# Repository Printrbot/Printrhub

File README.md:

# Printrhub

Welcome and thank you for your interest in our Printrhub technology. In this repository you will find everything you need to build upon the technology we invented. You may use the code and hardware to build your own devices or to improve your own Simple 2016. Please let us know about your projects and post issues or pull request to help us improve this project and code base.

## Purpose of the Printrhub

The Printrhub is the display component of our 3D printer Simple 2016 (http://printrbot.com/new-2016-simple/) and thus is the main user interface. The user can select, start, modify and pause prints or setup the printer with it. A fluid user interface controlled by touch as you know it from your smartphone let's anyone can start a print. The Hub also controls the printer and handles communication with the Printrbot cloud.

The Printrhub contains these components that form the final hardware

* ESP-12E module for WiFi connection and Over the Air updates
* MK20DX256LHV7 (Teensy 3) MCU is the main processor for handling the display, touch, SD card, controls the printer and ESP-12E
* 2.8 inch TFT display with 320x240 pixels
* Capacitive touch screen
* microSD card slot

As our board hosts two MCUs we need two different firmware, one for the ESP-12E module and the other one for the main MCU.

## Organization of this repository

* **/esp**: The firmware for the ESP-12E WiFi module
* **/mk20**: Contains the firmware for the main processor
* **/pcb**: Revisions 0.1, and 0.4 (final revision) of the PCB as Eagle and Copper files (for BOM and 3D views)
* **/utils**: The image tool that we use to build the ui.min file that contains all images used by the firmware combined in one file
* **/sdcard**: The initial content of the SD card that we ship with your printer (contains firmware images and root folder structure)
 
## Documentation
  
We have developed the hub in cooperation with Phillip Schuster (http://www.appfruits.com). He has written some documentation and behind the scenes reports that you should have read before working with our code and hardware.

### Behind the scenes of the Printrbot Simple 2016

How we started development and why we think you will learn something about product development in general.
http://www.appfruits.com/2016/11/behind-the-scenes-printrbot-simple-2016/

### Display System Explained

Expains the display and application framework in great detail. Explains the application flow, how to pseudo code multi threading and how implement a fast fluid and responsive user interface in a device capable of only 64 KB of RAM and 72 MHz.
http://www.appfruits.com/2016/11/printrbot-simple-2016-display-system-explained/

### CommStack explained

We invented CommStack to handle the communication between the MK20 and the ESP-12E module. It's fast, robust, bidirectional and features a nice request/response based system that enables two or more MCUs to communicate without having to handle all the little details.
http://www.appfruits.com/2016/11/printrbot-simple-2016-commstack-explained/

### Hardware explained

Describes the hardware in detail. Provides schematics, layout and details about the hardware we developed for the Printrbot hub.
http://www.appfruits.com/2016/11/printrbot-simple-2016-hardware-pcb-explained/

## Credits

Contains code or portions from these great libraries

* https://github.com/bakercp/PacketSerial
* https://github.com/PaulStoffregen/ILI9341_t3
* https://github.com/PaulStoffregen/ILI9341_fonts
* https://github.com/scanlime/esp8266-arm-swd
* https://github.com/esp8266/Arduino
* https://github.com/me-no-dev/ESPAsyncTCP.git
* https://github.com/me-no-dev/ESPAsyncWebServer.git
* https://github.com/bblanchon/ArduinoJson.git

Developed in cooperation with Phillip Schuster (@appfruits) from Appfruits (http://www.appfruits.com). Big thanks to Paul J. Stoffregen (https://www.pjrc.com/teensy/index.html) and his amazing Teensy project. It served as a great starting point and his amazing display driver for ILI9341 based display made our modern, fluid user interface possible.

## Support us

Printrbot invests time and resources providing this open source code, please support Printrbot and open-source hardware by purchasing products from Printrbot (http://www.printrbot.com)!

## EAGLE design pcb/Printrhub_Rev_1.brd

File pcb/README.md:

# Printrhub PCB

This repository contains two revisions of the PCB of the Printrhub. See main folder for more details about the project.

## Documentation and details

This PCB has been developed in cooperation by Phillip Schuster (http://www.appfruits.com). He has written a blog post about these PCBs and documents the details of it.
http://www.appfruits.com/2016/11/printrbot-simple-2016-hardware-pcb-explained/

## Revisions

This folder contains two revisions:

### Revision 0.1

This has been the first PCB we have created and contains the Teensy bootloader chip and an USB port that makes it easy to flash new firmware. It's basically just a bigger Teensy with more components. The firmware supports this revision, but you will need to set the correct #define in the HAL.h file in both firmwares

### Revision 0.4

This is the final revision we ship with the Simple 2016. Firmware must be flashed via SWD or our Over the Air update system.

## EAGLE and Copper files

These files can be opened with EAGLE, but you will need at least a Hobbyist license as we use 4-layers. We have also added Copper (http://www.copper-app.com) files that contain the complete BOM and a 3D view of the boards.

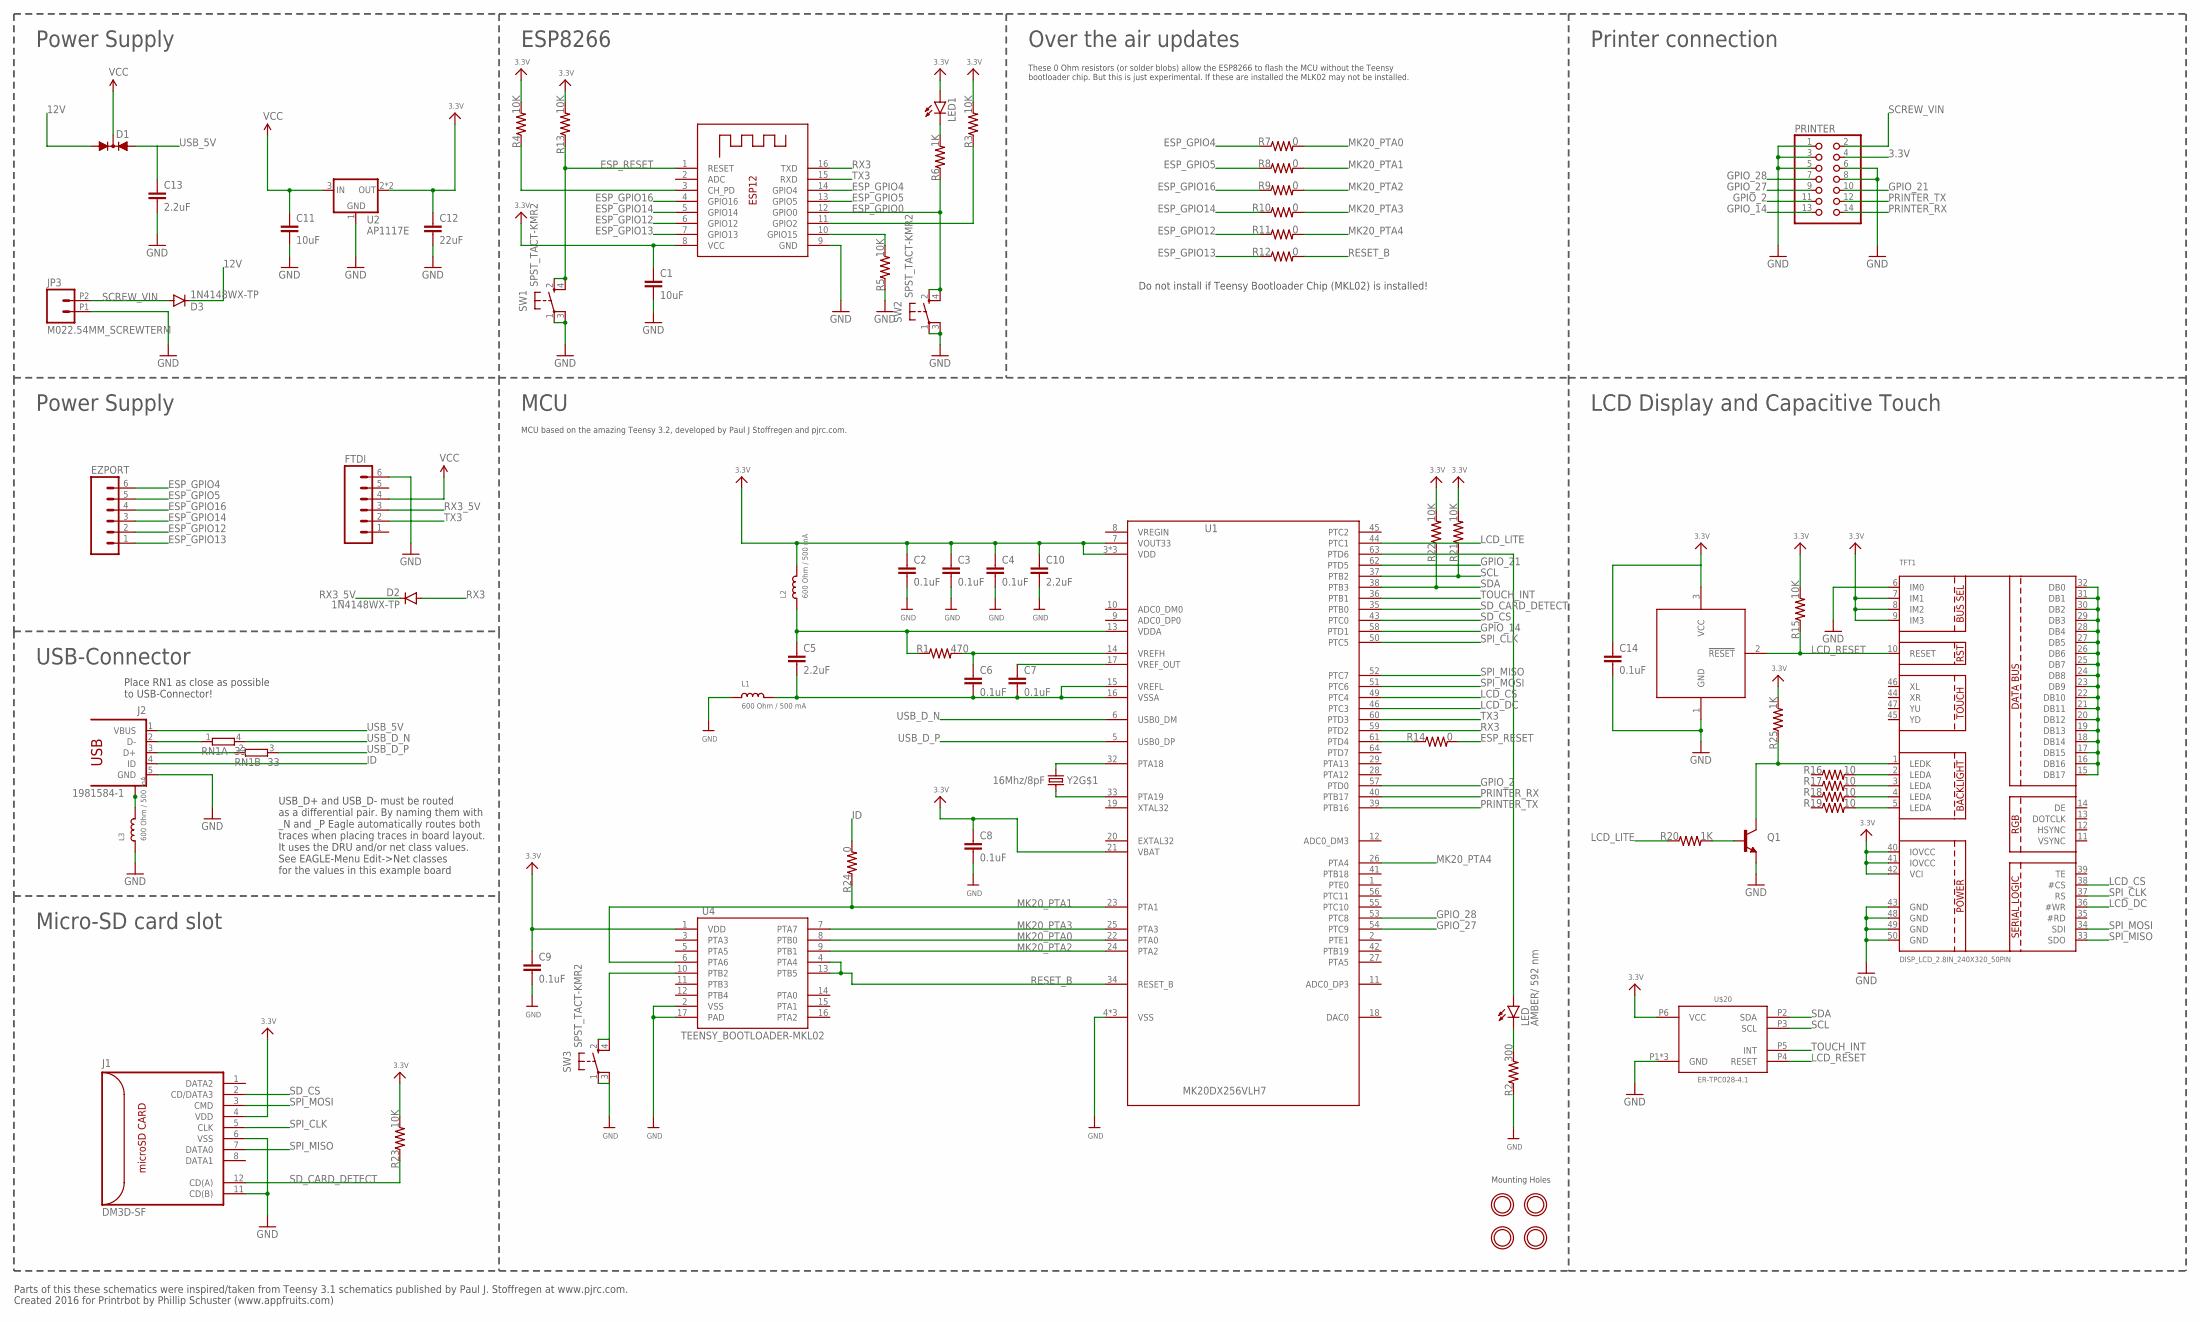
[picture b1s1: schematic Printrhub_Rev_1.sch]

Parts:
C1, C11: 10uF; 0603-CAP
C2, C3, C4, C6, C7, C8, C9, C14: 0.1uF; 0603-CAP
C5, C10, C13: 2.2uF; 0603-CAP
C12: 22uF; 0603-CAP
D1: DIODE-2AC|CASOT23; SOT23
D2, D3: 1N4148WX-TP; SOD-323; MPN 1N4148WX-TP
EZPORT: M06SMD-STRAIGHT; 1X06_SMD_STRAIGHT
FTDI: M06SMD-STRAIGHT; 1X06_SMD_STRAIGHT
J1: DM3D-SF
J2: 1981584-1
JP3: M022.54MM_SCREWTERM; 1X02_2.54_SCREWTERM
L1, L2, L3: 600 Ohm / 500 mA; 0603
LED: AMBER/ 592 nm; LED-0603
LED1: LED-GREEN; LED-0603
PRINTER: PINHD-2X7SMT; 2X07_SMT
Q1: TRANSISTOR_NPNSOT23-3; SOT23-3
R1: 470; 0603-RES
R2: 300; 0603-RES
R3, R4, R5, R13, R15, R21, R22, R23: 10K; 0603-RES
R6, R20, R25: 1K; 0603-RES
R7, R8, R9, R10, R11, R12, R14, R24: 0; 0603-RES
R16, R17, R18, R19: 10; 0603-RES
RN1: 33; EXB34V; MPN EXB-34V330JV
SW1, SW2, SW3: SPST_TACT-KMR2; KMR2
TFT1: DISP_LCD_2.8IN_240X320_50PIN; TFT_2.83IN_240X320_50PIN
U1: MK20DX256VLH7; MPN MK20DX256VLH7
U2: AP1117E; SOT223
U3: MAX308-SOT23; SOT23
U4: TEENSY_BOOTLOADER-MKL02; QFN50P300X300X100-17N
U$15, U$16, U$17, U$18: MOUNTINGHOLE2.0; MOUNTINGHOLE_2.0_PLATED
U$20: ER-TPC028-4.1; ER-CON06HB-1
X1: ESP-12
Y2: 16Mhz/8pF; CRYSTAL-SMD-5X3; MPN ECS-160-8-30B-CKM

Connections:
3.3V: C1.1, C2.1, C3.1, C4.1, C8.1, C9.1, C10.1, C12.1, C14.1, J1.4 (VDD), L2.2, LED1.A, PRINTER.4, R3.2, R4.2, R13.2, R15.2, R21.2, R22.2, R23.2, R25.2, TFT1.7 (IM1), TFT1.8 (IM2), TFT1.9 (IM3), TFT1.40 (IOVCC), TFT1.41 (IOVCC), TFT1.42 (VCI), U1.3 (VDD), U1.7 (VOUT33), U1.21 (VBAT), U1.30 (VDD), U1.48 (VDD), U2.2 (OUT), U2.4 (OUT), U3.3 (VCC), U4.1 (VDD), U$20.P6 (VCC), X1.8 (VCC)
12V: D1.1 (A1), D3.C
ESP_GPIO0: R6.1, SW2.2 (S), SW2.4 (S1), X1.12 (GPIO0)
ESP_GPIO4: EZPORT.6, R7.1, X1.14 (GPIO4)
ESP_GPIO5: EZPORT.5, R8.1, X1.13 (GPIO5)
ESP_GPIO12: EZPORT.2, R11.1, X1.6 (GPIO12)
ESP_GPIO13: EZPORT.1, R12.1, X1.7 (GPIO13)
ESP_GPIO14: EZPORT.3, R10.1, X1.5 (GPIO14)
ESP_GPIO16: EZPORT.4, R9.1, X1.4 (GPIO16)
ESP_RESET: R13.1, R14.2, SW1.2 (S), SW1.4 (S1), X1.1 (RESET)
GND: C1.2, C2.2, C3.2, C4.2, C8.2, C9.2, C10.2, C11.2, C12.2, C13.2, C14.2, FTDI.6, J1.6 (VSS), J1.11 (CD(B)), J2.5 (GND), JP3.P1 (1), L1.1, L3.1, PRINTER.1, PRINTER.3, PRINTER.5, PRINTER.6, PRINTER.8, Q1.2 (E), R2.1, R5.1, SW1.1, SW1.3 (P1), SW2.1, SW2.3 (P1), SW3.1, SW3.3 (P1), TFT1.6 (IM0), TFT1.43 (GND), TFT1.48 (GND), TFT1.49 (GND), TFT1.50 (GND), U1.4 (VSS), U1.31 (VSS), U1.47 (VSS), U2.1 (GND), U3.1 (GND), U4.2 (VSS), U4.17 (PAD), U$20.P1 (GND), U$20.PAD@0 (GND), U$20.PAD@1 (GND), X1.9 (GND)
GPIO_2: PRINTER.11, U1.57 (PTD0)
GPIO_14: PRINTER.13, U1.58 (PTD1)
GPIO_21: PRINTER.10, U1.62 (PTD5)
GPIO_27: PRINTER.9, U1.54 (PTC9)
GPIO_28: PRINTER.7, U1.53 (PTC8)
ID: J2.4 (ID), R24.2
LCD_CS: TFT1.38 (#CS), U1.49 (PTC4)
LCD_DC: TFT1.36 (#WR), U1.46 (PTC3)
LCD_LITE: R20.1, U1.44 (PTC1)
LCD_RESET: R15.1, TFT1.10 (RESET), U3.2 (!RESET), U$20.P4 (RESET)
MK20_PTA0: R7.2, U1.22 (PTA0), U4.8 (PTB0)
MK20_PTA1: R8.2, R24.1, U1.23 (PTA1), U4.6 (PTA6)
MK20_PTA2: R9.2, U1.24 (PTA2), U4.9 (PTB1)
MK20_PTA3: R10.2, U1.25 (PTA3), U4.7 (PTA7)
MK20_PTA4: R11.2, U1.26 (PTA4)
unnamed: R3.1, X1.11 (GPIO2)
unnamed: R4.1, X1.3 (CH_PD)
unnamed: R5.2, X1.10 (GPIO15)
unnamed: LED1.C, R6.2
unnamed: R14.1, U1.61 (PTD4)
unnamed: Q1.3 (C), R25.1, TFT1.1 (LEDK)
unnamed: R16.2, TFT1.2 (LEDA)
unnamed: LED.A, U1.63 (PTD6)
unnamed: R17.2, TFT1.3 (LEDA)
unnamed: R18.2, TFT1.4 (LEDA)
unnamed: R19.2, TFT1.5 (LEDA)
unnamed: Q1.1 (B), R20.2
unnamed: TFT1.15 (DB17), TFT1.16 (DB16), TFT1.17 (DB15), TFT1.18 (DB14), TFT1.19 (DB13), TFT1.20 (DB12), TFT1.21 (DB11), TFT1.22 (DB10), TFT1.23 (DB9), TFT1.24 (DB8), TFT1.25 (DB7), TFT1.26 (DB6), TFT1.27 (DB5), TFT1.28 (DB4), TFT1.29 (DB3), TFT1.30 (DB2), TFT1.31 (DB1), TFT1.32 (DB0)
unnamed: LED.C, R2.2
unnamed: U1.32 (PTA18), Y2.3 (2)
unnamed: U1.33 (PTA19), Y2.1
PRINTER_RX: PRINTER.14, U1.40 (PTB17)
PRINTER_TX: PRINTER.12, U1.39 (PTB16)
PROGRAM: SW3.2 (S), SW3.4 (S1), U4.10 (PTB2)
RESET_B: R12.2, U1.34 (RESET_B), U4.4 (PTA4), U4.13 (PTB5)
RX3: D2.A, U1.59 (PTD2), X1.16 (TXD)
RX3_5V: D2.C, FTDI.3
SCL: R21.1, U1.37 (PTB2), U$20.P3 (SCL)
SCREW_VIN: D3.A, JP3.P2 (2), PRINTER.2
SDA: R22.1, U1.38 (PTB3), U$20.P2 (SDA)
SD_CARD_DETECT: J1.12 (CD(A)), R23.1, U1.35 (PTB0)
SD_CS: J1.2 (CD/DATA3), U1.43 (PTC0)
SPI_CLK: J1.5 (CLK), TFT1.37 (RS), U1.50 (PTC5)
SPI_MISO: J1.7 (DATA0), TFT1.33 (SDO), U1.52 (PTC7)
SPI_MOSI: J1.3 (CMD), TFT1.34 (SDI), U1.51 (PTC6)
TOUCH_INT: U1.36 (PTB1), U$20.P5 (INT)
TX3: FTDI.2, U1.60 (PTD3), X1.15 (RXD)
USB_5V: C13.1, D1.2 (A2), J2.1 (VBUS)
USB_CON_N: J2.2 (D-), RN1.1
USB_CON_P: J2.3 (D+), RN1.2 (1)
USB_D_N: RN1.4 (2), U1.6 (USB0_DM)
USB_D_P: RN1.3 (2), U1.5 (USB0_DP)
USB_SHIELD: J2.S1, J2.S2, J2.S3, J2.S4, L3.2
VCC: C11.1, D1.3 (C), FTDI.4, U2.3 (IN)
VDDA: C5.1, L2.1, R1.1, U1.13 (VDDA)
VREFH: C6.1, R1.2, U1.14 (VREFH)
VREFL: C5.2, C6.2, C7.2, L1.2, U1.15 (VREFL), U1.16 (VSSA)
VREF_OUT: C7.1, U1.17 (VREF_OUT)

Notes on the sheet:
USB-Connector
ESP8266
MCU
MCU based on the amazing Teensy 3.2, developed by Paul J Stoffregen and pjrc.com.
Place RN1 as close as possible to USB-Connector!
USB_D+ and USB_D- must be routed as a differential pair. By naming them with _N and _P Eagle automatically routes both traces when placing traces in board layout. It uses the DRU and/or net class values. See EAGLE-Menu Edit->Net classes for the values in this example board
Parts of this these schematics were inspired/taken from Teensy 3.1 schematics published by Paul J. Stoffregen at www.pjrc.com.
Created 2016 for Printrbot by Phillip Schuster (www.appfruits.com)
Do not install if Teensy Bootloader Chip (MKL02) is installed!
Power Supply
Over the air updates
Micro-SD card slot
These 0 Ohm resistors (or solder blobs) allow the ESP8266 to flash the MCU without the Teensy bootloader chip. But this is just experimental. If these are installed the MLK02 may not be installed.
LCD Display and Capacitive Touch
Printer connection
Mounting Holes

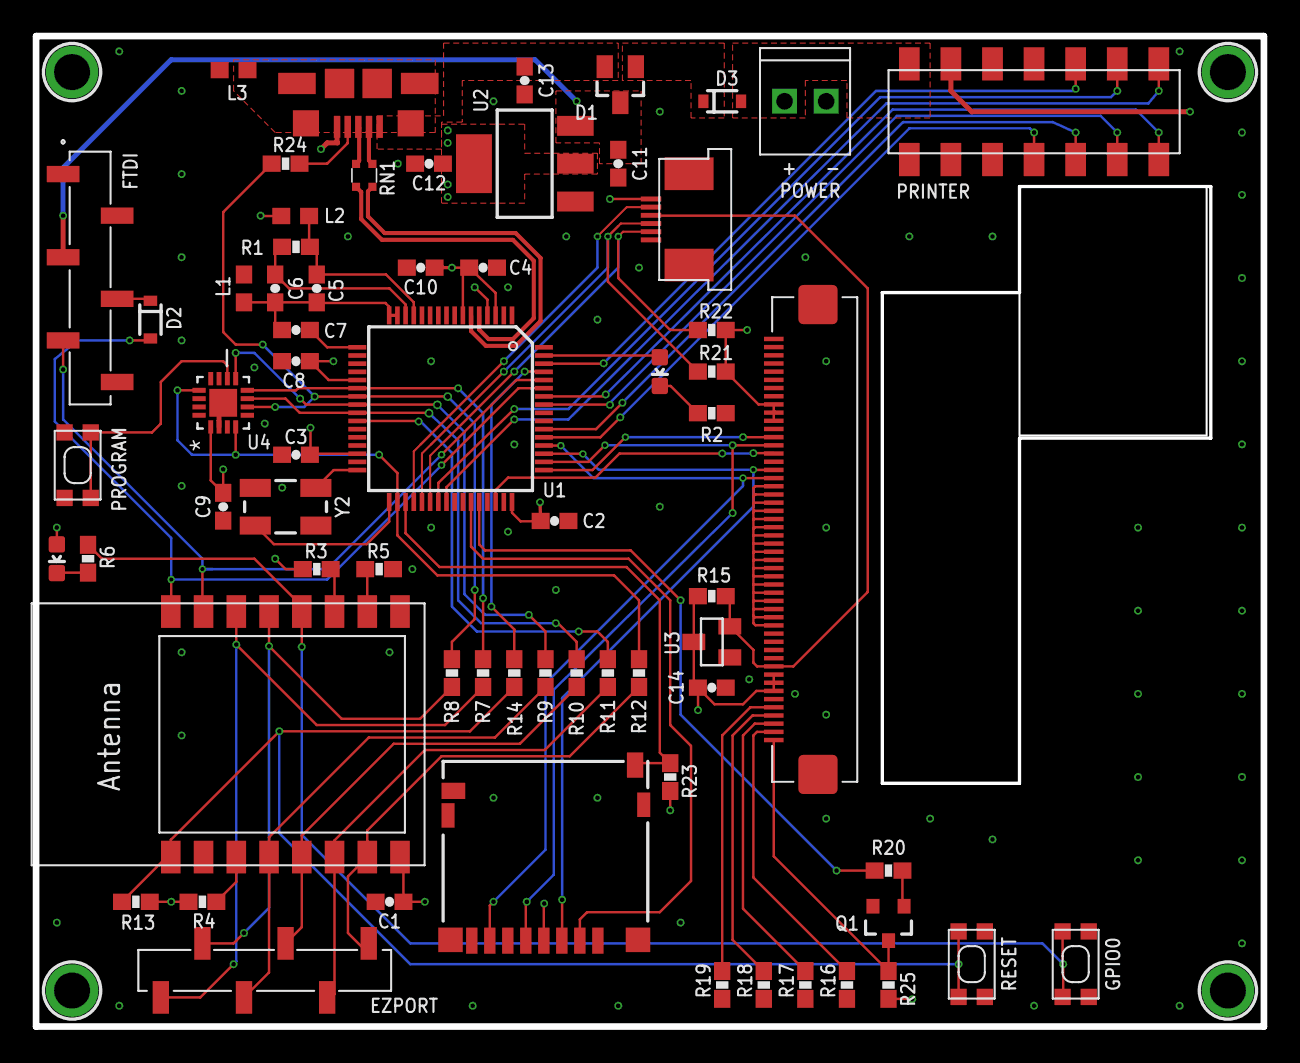
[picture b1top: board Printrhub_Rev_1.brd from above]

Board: 4 copper layers, 75.0 x 60.5 mm, 70 parts (1 on the bottom side), 69 nets.

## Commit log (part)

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2016-05-12 Added CLion files
2016-05-13 Some code cleanup
2016-05-13 Added physically based scrolling code (realistic acceleration and deceleration) with snapping and flicking multiple slots at once. Fixed a lot of bugs and fixed a few other smaller bugs. Added a lot 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
2016-05-13 Added some debug logs to View
2016-05-13 Added print button to print job selection and implemented basic application flow from selecting a job, pausing it, resuming and so on
2016-06-22 Made progress with section programming. Works now, but programmed application does not run.
2016-06-24 Added application framework for ESP8266 firmware like the one in the Printrhub MK20 firmware. I.e. having a global Application class that handles different modes that are pushed on the stack.
2016-07-09 Fixed a small bug in Rev 0.2 of the Printrhub PCB
2016-07-13 Implementation of file downloads with current CommStack architecture. Problem is it blocks the whole device and is not very reliable. Will switch to a more packet orientated style.
2016-07-14 Added file logger to the ESP firmware
2016-07-19 Optimized CommStack header
2016-07-25 Fixed a bug with way to many display updates for progress bar.
2016-07-26 Prepared SceneController for new Responses
2016-07-28 Modified FT6202 touch screen driver to improve performance while checking for touches. Reading from the FT6202 is quite slow via I2C but FT6202 has a special mode where interrupt pin can be set to be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
2016-07-28 Added a signal (pin 13) to show what the ESP is doing in the Logic Analyzer. Allows for better optimizations.
2016-07-28 Modified DownloadFileController to receive the file to download in the constructor.
2016-07-28 Added a HAL.h file that holds all pin definitions for different hardware revisions in one place.
2016-08-01 Removed or changed a few Serial.println debug logs as they don't work with 0.2 hardware revision
2016-08-01 Fixed a bug with missing checksum under certain conditions.
2016-08-01 ESP sends an error request to MK20 if downloading from the web failed. MK20 needs some code to handle that though
2016-08-01 Fixed a bug with missing checksums on ESP
2016-08-09 added readme file for mk20
2016-08-10 Added Revision 0.3 work in progress. Modified dimensions and display placement for final Simple design and rerouted traces accordingly.
2016-09-02 added pin init for G2 Reset and Erase pins
2016-09-02 esp updates...
2016-09-04 Fixed HAL bugs and added Rev 0.3
2016-09-04 Added support for Rev 0.3 when R8 is installed (R8 pulls RESET_B low, must be pulled high for the MK20 to start)
2016-09-06 Readded SCL1 and SDA1 (so this version is committed, too).
2016-09-08 Moved display 0.45mm to the right (from component side), moved some traces to make space and moved test points a bit to make them more centered above the SD card slot.
2016-09-13 added config for V3 hub
2016-09-13 updated layout
2016-09-13 added led
2016-09-13 new ui bitmaps
2016-09-16 Updated CLion workspace
2016-09-16 Added library reference to ArduinoJson in MK20 project
2016-09-16 Added CMakeListsPrivate.txt
2016-09-20 Fixed a few issues with FlashMK20 JLink script. MK20 is now setup so the GDBServer doesn't show strange errors when started directly after this script.
2016-09-21 Fixed various bugs when scrolling by adding a scroll offset that moves the visible "action" to the other side of the screen making it harder for the eye to see it. Also added a delay of 5 millis betw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
2016-09-22 Fixed a bug in PreheatExtruder. C-Strings must be strcompare'd as there is no default operator for const char. After this fix I was able to do a complete filament change complete with working progres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
2016-09-23 adding calibration scene
2016-09-23 When uploading the firmware via gdb it sometimes locked up. This change prevents that and works fine.
2016-09-26 adding two full print projects for print testing
2016-09-27 CommStack TaskIDs are now scoped enumeration meaning that enum values aren't defined in global scope meaning less confusing error codes when compiling and better code structure. (+1 squashed commit) 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
2016-09-27 Fixed a bug in ImageBuffer
2016-09-27 Fixed a bug with graphical glitches when scrolling
2016-09-27 Added job downloads and reworked JobsScene to be a bit more MVC, i.e. a Job structure holds the job info and ImageView just shows them. When the button is pressed the correct Job is selected from the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
2016-09-27 adding more jobs to sd card for testing
2016-09-28 updated project index
    Added revision info to project and job (in project index file), and
    number of times job has been printed. Also updated Job and Project
    status scenes to be able to read new index files correctly.
2016-09-28 added project sidebar bitmap
2016-09-28 changed progress bar color (not working) and updated white space formatting (spaces vs tabs)
2016-09-28 adding another parameter to default printrCallback method
2016-09-29 implemented saving hotend offset to eeprom
2016-09-29 Added a CommStack marker pin action to see HttpClient activity in Logic Analyzer
2016-09-29 Modified FasterWiFiClient code
2016-09-30 Added debug configuration for debugging MK20 with J-Link
2016-09-30 Prepared (manual) firmware update cycle
2016-10-06 Refactored code and implemented alive state on both MCUs. Both MCUs keep state of the other MCU and if unknown both send pings until connection is stable. This is preparation for automatic firmware u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
2016-10-08 Added firmware update cycle, added mode chaining to ESP modes that allows to chain modes together in advance and ESP will run them in subsequent order. Added new firmware UI to MK20 firmware and new 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
2016-10-08 Rebuild DownloadURL mode to use the (much faster) ESPHttpClient than the HttpClient used before.
2016-10-08 Added support for hardware supported debug serial out of MK20 through Serial2
2016-10-09 cleaned up web services, added wifi setup and network scan json output
2016-10-10 added materials button to settings scene instead of jobs
2016-10-10 display different print button based on if job is already downloaded...
2016-10-11 added job cancel to print status scene
2016-10-11 increased the size of buffer in event logger since it was cutting out the url
2016-10-12 added additional info to print status scene and printr class
    Print time, resolution, infill, print support and filament required…
2016-10-13 Pimped background jobs and fixed some bugs.
2016-10-13 Added possibility to trigger firmware update via HTTP request
2016-10-13 Downloads to SD card appended the files to the previous file. Fixed now.
2016-10-13 If MK20 got shot off in between ESP ran into an infinite loop. Should be fixed now.
2016-10-13 Added updating MK20 without UI
2016-10-13 adding missing images for ui
2016-10-13 Added system info and a possibility to show them on screen.
2016-10-13 Latest MK20 firmware
2016-10-14 Increased JSON buffer for parsing firmware update to have enough space for later addition of files and values
2016-10-16 Removed unused code
2016-10-16 Solved issues with response parsing from printer
2016-10-16 removed old image tool folder from the repo and moved new one from root directory into utils folder. Also added new splash image and ui files
2016-10-17 Modified Printer class to do all communication with printer asynchronous even for setup, startup and clearance GCode.
2016-10-17 Added example implementation for basic http authentication with /info event
2016-10-24 Bugfix in MemoryStream fixes bug with printer stopping to print after initial startup code is sent.
2016-10-24 Modified Printr class to send multiple lines before waiting for a response (corresponds to g2 documentation of bursting in 4 lines at startup). Comments are skipped now. Added massive logs to show er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
2016-10-25 Do not print a newline in log messages when the log message already contains a newline
2016-10-25 Removed version numbers again as they did not work (although documented by PlatformIO).
2016-10-25 When downloading a new project show that project after download is complete instead of always the first one.
2016-10-25 Implemented nextScene in downloadFileController
2016-10-25 added line numbers to outgoing gcode and updated bed probing positions
2016-10-25 Added another log macro
2016-10-25 Modified Printr class to end print only when stat:4 message came in and not at EOF.
2016-10-26 fixed close button to allow it to exit current scene
2016-10-26 Added wait commands to load and unload filament
2016-10-27 temporary commented out the code that was causing setScrollOffset to shift to the wrong value
2016-10-27 Fixed the bug in calibrate scene with corrupted hotend offset text. Requires an updated ui.min on SD card.
2016-10-27 updated gcode and set progress bar to red color
2016-10-27 changed default highlight background color
2016-10-27 updated splash screen and added two new bitmaps for firmware load/unload
2016-10-27 Replaced Printr class with latest version from GoodPrintr
2016-10-28 reset _progress to 0.0 on start of new job
    this issue has been preventing new job to from starting after
    successful print
2016-10-28 Replaced addScrollOffset with the new function setScrollOffset to set the (initial) scroll offset of a scene.
2016-10-28 Fixed a bug with load/unload filament. Fixes #28
2016-10-31 added project index to track order of project files
    Also updated project and job scene and simplified reading file index
    #25
2016-10-31 prevent new project download while printer is busy printing
    Print status scene is now modal, which prevents any new screen from
    interrupting it (unless it is on button press). This fixes bug #30
2016-10-31 fixed bug #23
    removed stat3 check that was causing print to finish before it starts.
    Stat 3 means that G2 queue is empty, not that print job is finished,
    and it can happen in the middle of the job (if there are a lot of small
    moves that get consumed faster then queue can be populated)
2016-11-01 Print flag is now reset when print is stopped
2016-11-01 Added Set Password dialog, virtual keyboard and CommStack event handling. Setting an empty password clears it. Fixes #18
2016-11-01 Only update progress bar every second to keep pressure on system low even when progress changes each frame.
2016-11-01 Modified ARM flasher to use EventLogging for debug logs
2016-11-02 Web app requests with OPTIONS method to get info about methods and authentication. Added that for /info. Authentication now works. #11
2016-11-02 fixed issue with wrong colors in generated uncompressed ui file
2016-11-03 Renamed downloaded local firmware filename from mk20_100.bin to mk20.bin
2016-11-06 Removed special progress bar handling after printer is stopped. This did not work and introduced other bugs. Fixes #37
2016-11-06 Removed code that prevented progress bar to be rendered in between 5% steps. Progress bar is handling fast changes better now so this could be removed.
2016-11-09 added startListening and stopListening methods
    this can be used when we want to listen for the printer responses, and
    to stop printer from sending anything back to hub when we are not
    listening for events. It looks like this also fixed remaining issues in
    bug #36 and #32 where download was failing while printer hotend was hot
    (and sending messages back to hub)
2016-11-09 implemented materials selection scenes
2016-11-09 Fixes a bug with non-scrolling scenes are either blank or can be scrolled. Fixes #38
2016-11-10 implemented serial number on mk20 - #40
2016-11-21 Added README.md
2016-11-21 Removed older code from main.cpp
2016-11-21 Removed unused ModelView
2016-11-21 Added authors and links to documentation (ESP firmware)
2016-11-24 Fixed some bugs in README.MD
2016-12-08 remove unused header.
2016-12-12 replaced update icon with light icon
2016-12-12 adjusted icon position
2016-12-12 removed idleSceneController
2017-02-13 removed estimated print time from print status screen
2017-02-14 removed brand text
2017-02-14 updating image library with new bitmaps
2017-02-17 added beta firmware url for testing
2017-02-24 Mac address is now displayed in Wifi setup HTML page. Fixes #9
2018-02-09 Fixed a compilation bug with characters in keyboard that don’t fit in a char.

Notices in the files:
parts and their libraries:
con-sd-card: Copyright (C) 2008, Bob Starr
SparkFun-Connectors: Licensing: Creative Commons ShareAlike 4.0 International - https://creativecommons.org/licenses/by-sa/4.0
